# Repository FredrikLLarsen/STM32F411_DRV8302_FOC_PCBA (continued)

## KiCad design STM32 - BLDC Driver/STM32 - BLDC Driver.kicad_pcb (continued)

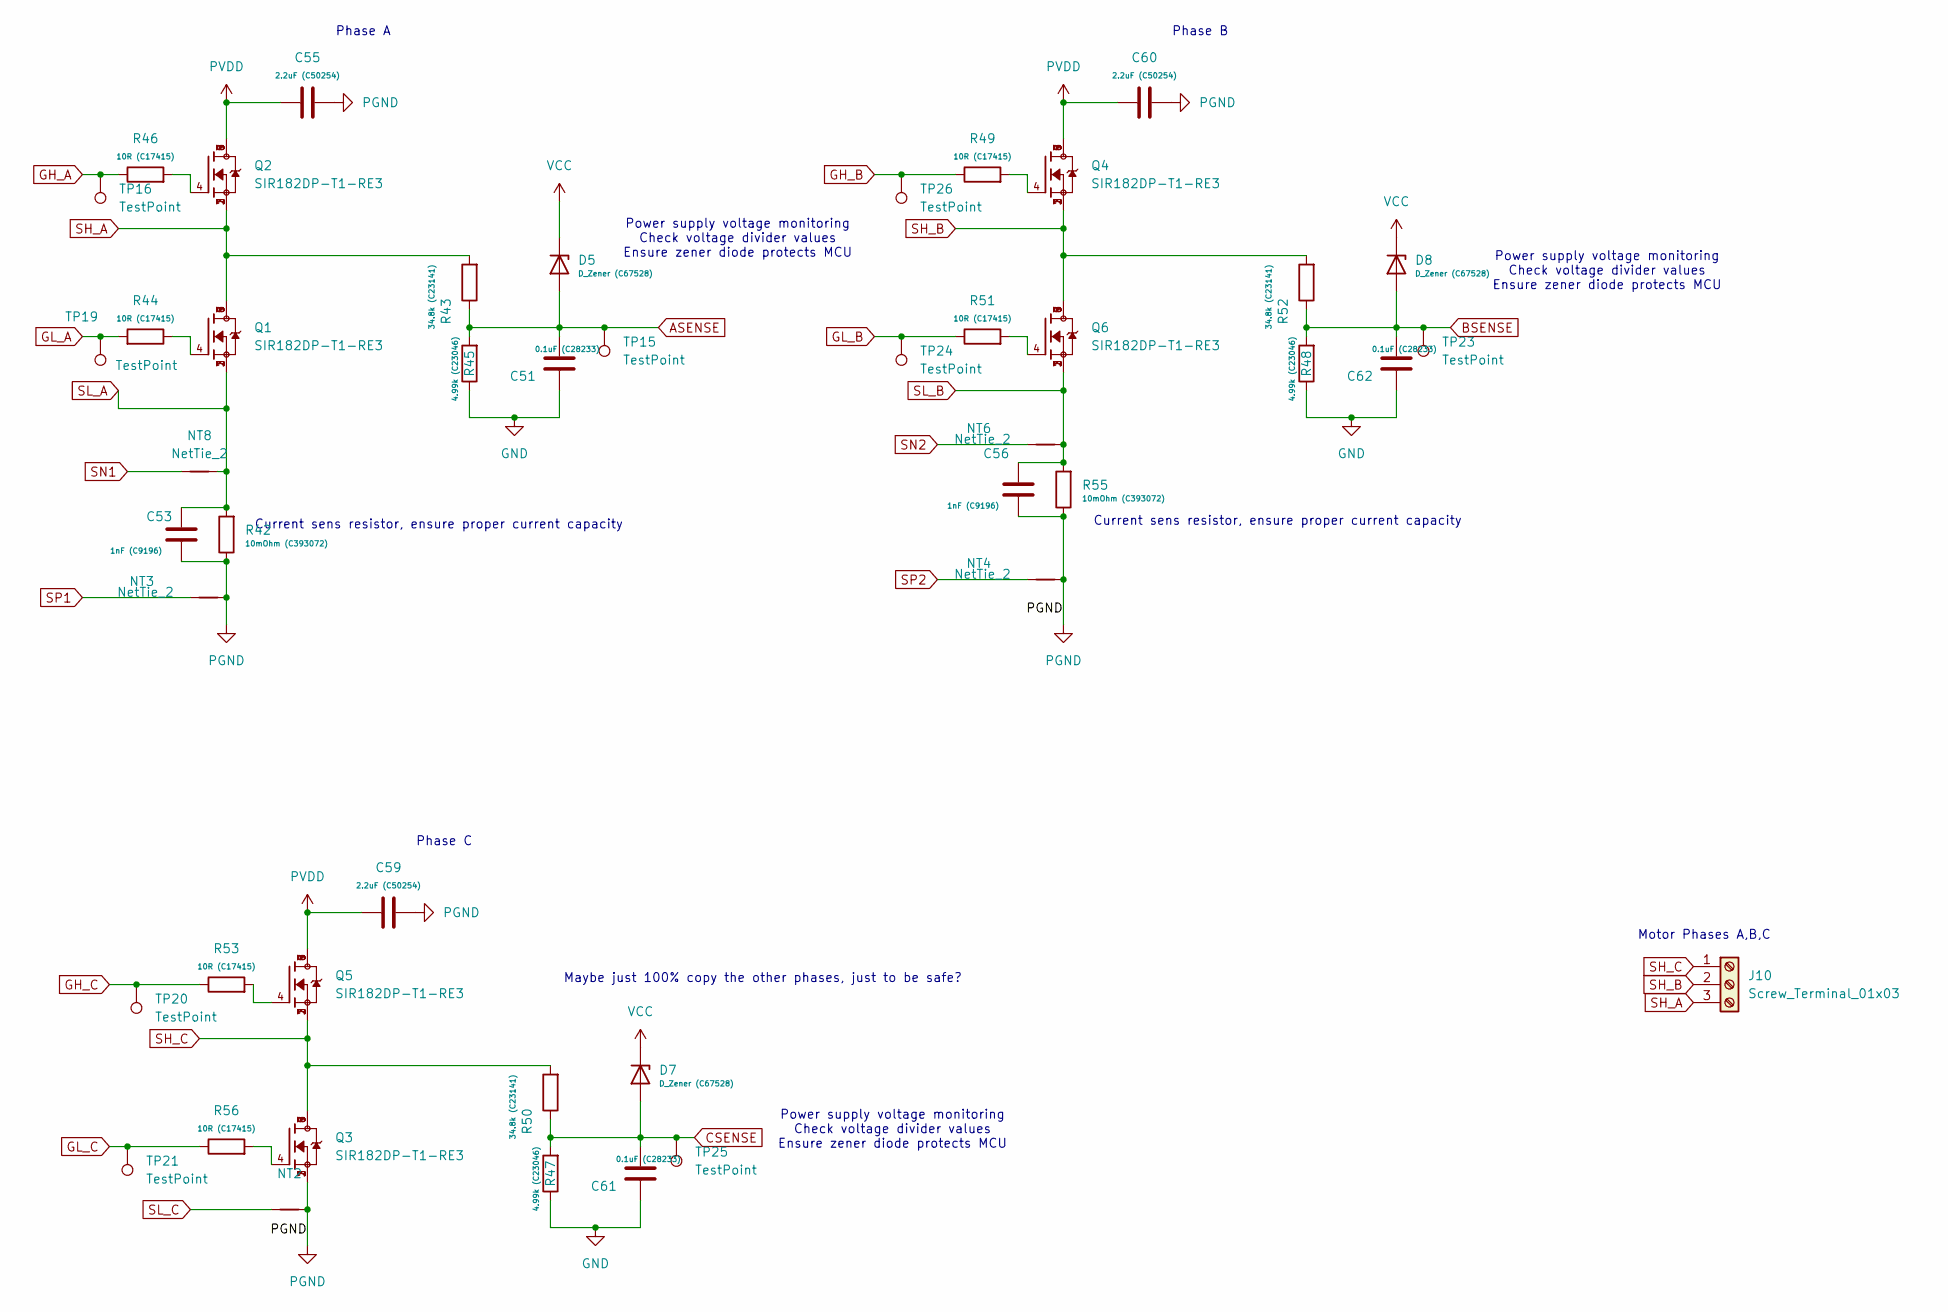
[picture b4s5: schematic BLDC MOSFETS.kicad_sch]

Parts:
C51, C61, C62: 0.1uF (C28233); C_0805_2012Metric_Pad1.18x1.45mm_HandSolder
C53: 1nF (C9196); C_1206_3216Metric
C55, C59, C60: 2.2uF (C50254); C_1206_3216Metric_Pad1.33x1.80mm_HandSolder
C56: 1nF (C9196); C_1206_3216Metric_Pad1.33x1.80mm_HandSolder
D5, D7, D8: D_Zener (C67528); D_SOD-323
J10: Screw_Terminal_01x03; TerminalBlock_bornier-3_P5.08mm
NT2, NT3, NT4, NT6, NT8: NetTie_2; NetTie-2_SMD_Pad0.5mm
Q1, Q2, Q3, Q4, Q5, Q6: SIR182DP-T1-RE3; TRANS_SIR182DP-T1-RE3; PARTREV B
R42, R55: 10mOhm (C393072); R_2512_6332Metric_Pad1.40x3.35mm_HandSolder
R43, R50, R52: 34.8k (C23141); R_0603_1608Metric_Pad0.98x0.95mm_HandSolder
R44, R46, R49, R51, R53, R56: 10R (C17415); R_0805_2012Metric_Pad1.20x1.40mm_HandSolder
R45, R47, R48: 4.99k (C23046); R_0603_1608Metric_Pad0.98x0.95mm_HandSolder
TP15, TP16, TP19, TP20, TP21, TP23, TP24, TP25, TP26: TestPoint; TestPoint_Pad_D3.0mm

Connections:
+3V3: D5.1 (K), D7.1 (K), D8.1 (K); also elsewhere on the board
ASENSE: C51.2, D5.2 (A), R43.1, R45.2, TP15.1; also elsewhere on the board
BSENSE: C62.2, D8.2 (A), R48.2, R52.1, TP23.1; also elsewhere on the board
CSENSE: C61.2, D7.2 (A), R47.2, R50.1, TP25.1; also elsewhere on the board
GH_A: R46.1, TP16.1; also elsewhere on the board
GH_B: R49.1, TP26.1; also elsewhere on the board
GH_C: R53.1, TP20.1; also elsewhere on the board
GL_A: R44.2, TP19.1; also elsewhere on the board
GL_B: R51.1, TP24.1; also elsewhere on the board
GL_C: R56.1, TP21.1; also elsewhere on the board
GND: C51.1, C61.1, C62.1, R45.1, R47.1, R48.1; also elsewhere on the board
unnamed: Q1.4, R44.1
unnamed: Q2.4, R46.2
unnamed: Q3.4, R56.2
unnamed: Q4.4, R49.2
unnamed: Q5.4, R53.2
unnamed: Q6.4, R51.2
PGND: C53.1, C55.2, C56.1, C59.2, C60.2, NT2.1, NT3.2, NT4.2, Q3.1, Q3.2, Q3.3, R42.1, R55.1; also elsewhere on the board
PVDD: C55.1, C59.1, C60.1, Q2.5, Q2.6, Q2.7, Q2.8, Q2.9, Q4.5, Q4.6, Q4.7, Q4.8, Q4.9, Q5.5, Q5.6, Q5.7, Q5.8, Q5.9; also elsewhere on the board
SH_A: J10.3, Q1.5, Q1.6, Q1.7, Q1.8, Q1.9, Q2.1, Q2.2, Q2.3, R43.2; also elsewhere on the board
SH_B: J10.2, Q4.1, Q4.2, Q4.3, Q6.5, Q6.6, Q6.7, Q6.8, Q6.9, R52.2; also elsewhere on the board
SH_C: J10.1, Q3.5, Q3.6, Q3.7, Q3.8, Q3.9, Q5.1, Q5.2, Q5.3, R50.2; also elsewhere on the board
SL_A: C53.2, NT8.2, Q1.1, Q1.2, Q1.3, R42.2; also elsewhere on the board
SL_B: C56.2, NT6.2, Q6.1, Q6.2, Q6.3, R55.2; also elsewhere on the board
SL_C: NT2.2; also elsewhere on the board
SN1: NT8.1; also elsewhere on the board
SN2: NT6.1; also elsewhere on the board
SP1: NT3.1; also elsewhere on the board
SP2: NT4.1; also elsewhere on the board

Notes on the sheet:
Power supply voltage monitoring Check voltage divider values Ensure zener diode protects MCU
Phase C
Current sens resistor, ensure proper current capacity
Motor Phases A,B,C
Phase B
Phase A
Maybe just 100% copy the other phases, just to be safe?

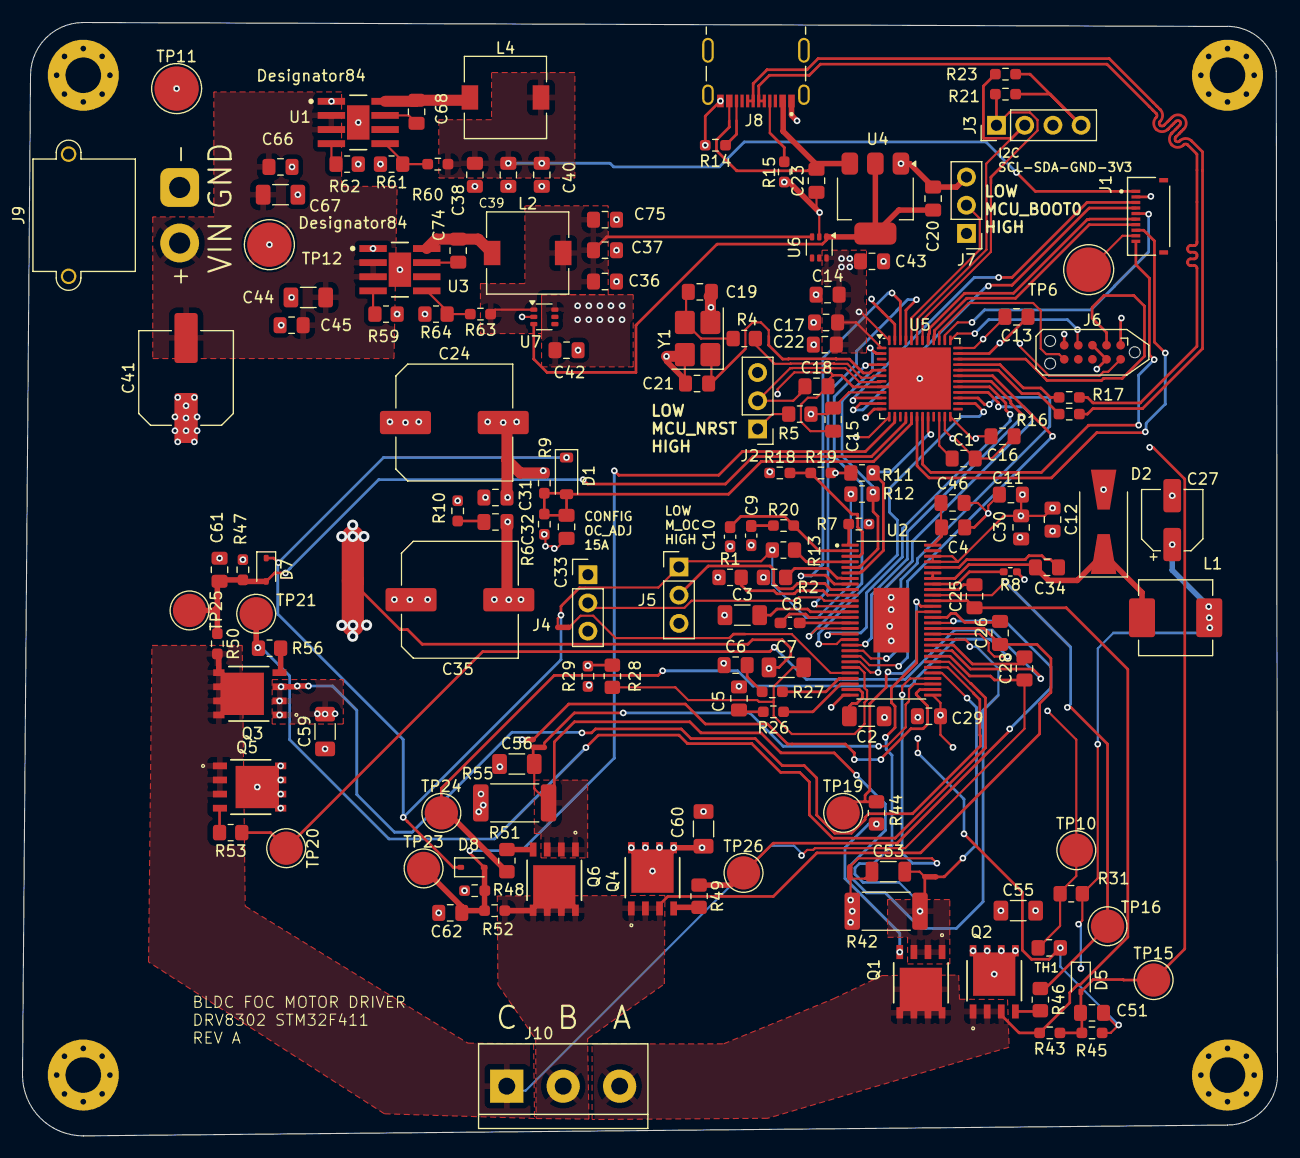
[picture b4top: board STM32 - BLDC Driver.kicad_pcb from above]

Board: 4 copper layers, 113.0 x 100.2 mm, 162 parts (0 on the bottom side), 109 nets.

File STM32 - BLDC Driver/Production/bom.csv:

Designator,Footprint,Quantity,Value,LCSC Part #
"C1, C11, C12, C42, C43",0805,5,4.7u low esr (C1779),
C10,0603,1,120p (C107035),
"C13, C14, C15, C16, C18, C19, C21, C22, C23, C45, C66",0805,11,100nF 50V (C28233),
C17,0805,1,2.2u (C5448893),
"C2, C7",1206,2,1uF (C13832),
C20,0805,1,10uF (C15850),
"C24, C35",C_Elec_10x10.2,2,220uF (C46550422),
"C25, C26, C28, C29, C30, C31, C33, C34, C51, C61, C62, C68, C74",0805,13,0.1uF (C28233),
C27,CP_Elec_5x5.4,1,47uF_P (C18221497),
C3,1206,1,2.2uF (C920964),
C32,0805,1,0.01uF (C1710),
"C36, C37, C38, C39, C40, C75",0805,6,22uF (C45783),
C4,0805,1,10nF (C1710),
C41,C_Elec_8x10.2,1,100uF 63V (C7471891),
"C44, C67",1206,2,4.7uF 50V (C29823),
C46,0805,1,4.7nF (C1744),
"C5, C6",0805,2,2.2nF (C28260),
"C53, C56",1206,2,1nF (C9196),
"C55, C59, C60",1206,3,2.2uF (C50254),
C8,0603,1,22nF (C376821),
C9,0603,1,6.8n (C1631),
D1,D_SOD-123,1,D_Zener (C173406),
D2,D_SMA-SMB_Universal_Handsoldering,1,B330A-13-F (C110485),
"D5, D7, D8",D_SOD-323,3,D_Zener (C67528),
J1,HRS_FH34SRJ-10S-0.5SH_50_,1,FH34SRJ-10S-0.5SH_50_,
J10,TerminalBlock_bornier-3_P5.08mm,1,Screw_Terminal_01x03,
"J2, J4, J5, J7",PinHeader_1x03_P2.54mm_Vertical,4,Conn_01x03_Pin,
J3,PinHeader_1x04_P2.54mm_Vertical,1,Conn_01x04_Pin,
J8,G-SWITCH_GT-USB-7010B,1,GT-USB-7010B,
J9,AMASS_XT30PW-M_1x02_P2.50mm_Horizontal,1,Conn_01x02_Pin,
L1,L_Changjiang_FXL0630,1,22uH (C177244),
"L2, L4",L_7.3x7.3_H3.5,2,15uH (C216196),
"Q1, Q2, Q3, Q4, Q5, Q6",TRANS_SIR182DP-T1-RE3,6,SIR182DP-T1-RE3,
"R1, R11, R12, R13, R2, R5",0805,6,10k (C17414),
R10,0603,1,3.3R (C22979),
"R14, R15",0603,2,5.1k (C22356620),
"R16, R17",0603,2,0R,
R18,0603,1,3k3 (C22356670),
R19,0603,1,18k (C2907111),
R20,0603,1,15k (C22356635),
"R21, R23",0603,2,2.2k (C4190),
"R26, R27",0603,2,56R (C2930118),
R28,0603,1,1k (C22356624),
R29,0805,1,80.6k (C2960781),
R31,0805,1,8.2k (C17828),
R4,0805,1,0R (C17477),
"R42, R55",2512,2,10mOhm (C393072),
"R43, R50, R52, R9",0603,4,34.8k (C23141),
"R44, R46, R49, R51, R53, R56",0805,6,10R (C17415),
"R45, R47, R48, R6",0603,4,4.99k (C23046),
"R59, R62",0805,2,64.9k (C17788),
R60,0603,1,100k (C15458),
"R61, R64",0805,2,24.9k (C17571),
R63,0603,1,57.6k (C204216),
R7,0603,1,200k (C25811),
R8,0402,1,1M (C26083),
TH1,0805,1,CMFB103F3950FANT (C51597),
"TP10, TP15, TP16, TP19, TP20, TP21, TP23, TP24, TP25, TP26",TestPoint_Pad_D3.0mm,10,TestPoint,
"TP11, TP12, TP6",TestPoint_Pad_D4.0mm,3,TestPoint,
"U1, U3",DDA0008E-IPC_A,2,LMR38020SDDAR,
U2,SOP50P810X120-57N,1,DRV8302DCAR,
U4,SOT-223-3_TabPin2,1,LD1117S33TR_SOT223,
U5,QFN-48-1EP_7x7mm_P0.5mm_EP5.6x5.6mm,1,STM32F411CEUx,
"U6, U7",SOT-363_SC-70-6,2,LM66100DCK,
Y1,Crystal_SMD_3225-4Pin_3.2x2.5mm_HandSoldering,1,Crystal_GND24 (C5444547),

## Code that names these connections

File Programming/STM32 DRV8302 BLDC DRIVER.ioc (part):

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Mcu.Name=STM32F411C(C-E)Ux
Mcu.Package=UFQFPN48
Mcu.UserName=STM32F411CEUx
PA0-WKUP.GPIOParameters=GPIO_Label
PA0-WKUP.GPIO_Label=QUAD_A_TIM2CH1
PA0-WKUP.Signal=S_TIM2_CH1_ETR
PA1.GPIOParameters=GPIO_Label
PA1.GPIO_Label=QUAD_B_TIM2CH2
PA1.Signal=S_TIM2_CH2
PA10.GPIOParameters=GPIO_Label
PA10.GPIO_Label=INH_C_TIM1_CH3
PA10.Signal=S_TIM1_CH3
PA11.Mode=Device_Only
PA11.Signal=USB_OTG_FS_DM
PA12.Mode=Device_Only
PA12.Signal=USB_OTG_FS_DP
PA13.Mode=Trace_Asynchronous_SW
PA13.Signal=SYS_JTMS-SWDIO
PA14.Mode=Trace_Asynchronous_SW
PA14.Signal=SYS_JTCK-SWCLK
PA15.GPIOParameters=GPIO_Label
PA15.GPIO_Label=QUAD_Z_EXTI15
PA15.Signal=GPXTI15
PA2.GPIOParameters=GPIO_Label
PA2.GPIO_Label=A_SENSE_ADC1_IN2
PA2.Signal=ADCx_IN2
PA3.GPIOParameters=GPIO_Label
PA3.GPIO_Label=MOS1_NTC
PA3.Signal=ADCx_IN3
PA4.GPIOParameters=GPIO_Label
PA4.GPIO_Label=B_SENSE_ADC1_IN4
PA4.Signal=ADCx_IN4
PA6.GPIOParameters=GPIO_Label
PA6.GPIO_Label=C_Sense_ADC1_IN6
PA6.Signal=ADCx_IN6
PA7.GPIOParameters=GPIO_Label
PA7.GPIO_Label=PVDDSENSE
PA7.Signal=ADCx_IN7
PA8.GPIOParameters=GPIO_Label
PA8.GPIO_Label=INH_A_TIM1_CH1
PA8.Signal=S_TIM1_CH1
PA9.GPIOParameters=GPIO_Label
PA9.GPIO_Label=INH_B_TIM1_CH2
PA9.Signal=S_TIM1_CH2
PB0.GPIOParameters=GPIO_Label
PB0.GPIO_Label=HALLZ_TIM3CH3
PB0.Signal=S_TIM3_CH3
PB1.Signal=ADCx_IN9
PB13.GPIOParameters=GPIO_Label
PB13.GPIO_Label=INL_A_TIM1_CH1N
PB13.Mode=PWM Generation1 CH1 CH1N
PB13.Signal=TIM1_CH1N
PB14.GPIOParameters=GPIO_Label
PB14.GPIO_Label=INL_B_TIM1_CH2N
PB14.Mode=PWM Generation2 CH2 CH2N
PB14.Signal=TIM1_CH2N
PB15.GPIOParameters=GPIO_Label
PB15.GPIO_Label=INL_C_TIM1_CH3N
PB15.Mode=PWM Generation3 CH3 CH3N
PB15.Signal=TIM1_CH3N
PB2.GPIOParameters=GPIO_Label
PB2.GPIO_Label=nFault - GPIO INPUT
PB2.Signal=GPIO_Input
PB3.Mode=Trace_Asynchronous_SW
PB3.Signal=SYS_JTDO-SWO
PB4.GPIOParameters=GPIO_Label
PB4.GPIO_Label=HALL_B_TIM3CH1
PB4.Signal=S_TIM3_CH1
PB5.GPIOParameters=GPIO_Label
PB5.GPIO_Label=HALL_A_TIM3CH2
PB5.Signal=S_TIM3_CH2
PB6.Mode=I2C
PB6.Signal=I2C1_SCL
PB7.Mode=I2C
PB7.Signal=I2C1_SDA
PB8.GPIOParameters=GPIO_Label
PB8.GPIO_Label=DC_CAL_GPIO_OUTPUT
PB8.Signal=GPIO_Output
PB9.GPIOParameters=GPIO_Label
PB9.GPIO_Label=DRV_M_PWM_GPIO_OUTPUT
PB9.Signal=GPIO_Output
PC13-ANTI_TAMP.GPIOParameters=GPIO_Label
PC13-ANTI_TAMP.GPIO_Label=nOCTW - GPIO INPUT
PC13-ANTI_TAMP.Signal=GPIO_Input
PC14-OSC32_IN.GPIOParameters=GPIO_Label
PC14-OSC32_IN.GPIO_Label=AS5600_PWM GPIO_INPUT
PC14-OSC32_IN.Signal=GPIO_Input
PC15-OSC32_OUT.Signal=GPIO_Output
PH0\ -\ OSC_IN.Mode=HSE-External-Oscillator
PH0\ -\ OSC_IN.Signal=RCC_OSC_IN
PH1\ -\ OSC_OUT.Mode=HSE-External-Oscillator
PH1\ -\ OSC_OUT.Signal=RCC_OSC_OUT
RCC.HSE_VALUE=16000000
RCC.SYSCLKFreq_VALUE=72000000
RCC.SYSCLKSource=RCC_SYSCLKSOURCE_PLLCLK
board=custom

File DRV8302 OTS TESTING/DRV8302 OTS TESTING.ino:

// Blink a pin on Arduino
// Change pin number if needed
const int EN_GATE = 8;
const int M_PWM = 9;
const int INL_C = 10;
const int INH_C = 11;

void setup() {
  pinMode(EN_GATE, OUTPUT);   // Set pin as output
  pinMode(M_PWM, OUTPUT);   // Set pin as output
  pinMode(INL_C, OUTPUT);   // Set pin as output
  pinMode(INH_C, OUTPUT);   // Set pin as output
}

void loop() {
  digitalWrite(EN_GATE, HIGH);  // Turn pin ON
  digitalWrite(M_PWM, LOW);  // Turn pin LOW
  digitalWrite(INL_C, LOW);  // Turn pin LOW
  digitalWrite(INH_C, HIGH);  // Turn pin LOW

}

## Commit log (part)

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2025-08-23 Initial upload
2025-08-24 Started assigning footprints
2025-08-24 Footprints
